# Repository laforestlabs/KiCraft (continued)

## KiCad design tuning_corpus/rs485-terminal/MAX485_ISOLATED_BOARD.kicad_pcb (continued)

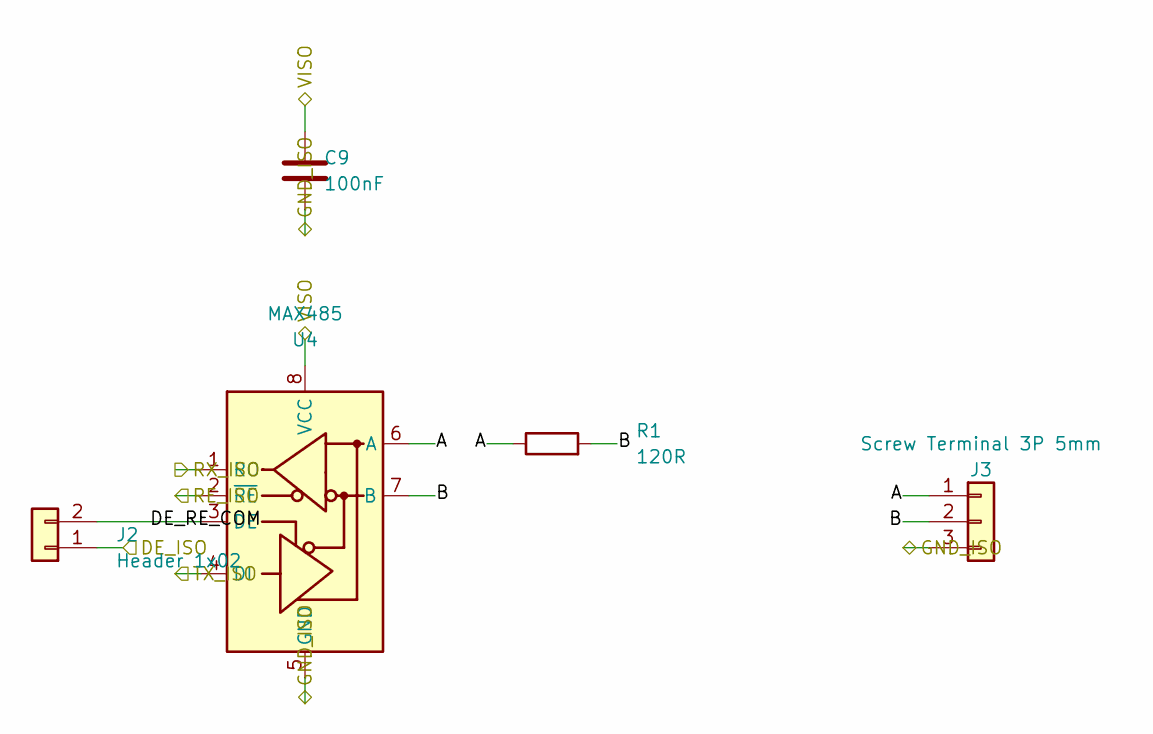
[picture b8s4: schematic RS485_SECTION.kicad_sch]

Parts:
C9: 100nF; C_0805_2012Metric
J2: Header 1x02; PinHeader_1x02_P2.54mm_Vertical
J3: Screw Terminal 3P 5mm; TerminalBlock_MaiXu_MX126-5.0-03P_1x03_P5.00mm
R1: 120R; R_0805_2012Metric
U4: MAX485; SOIC-8_3.9x4.9mm_P1.27mm

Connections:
A: J3.1, R1.1, U4.6 (A)
B: J3.2, R1.2, U4.7 (B)
DE_ISO: J2.1; also elsewhere on the board
DE_RE_COM: J2.2, U4.3 (DE)
GND_ISO: C9.2, J3.3, U4.5 (GND); also elsewhere on the board
RE_ISO: U4.2 (~RE); also elsewhere on the board
RX_ISO: U4.1 (RO); also elsewhere on the board
TX_ISO: U4.4 (DI); also elsewhere on the board
VISO: C9.1, U4.8 (VCC); also elsewhere on the board

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
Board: 2 copper layers, 17 parts (0 on the bottom side), 15 nets, no tracks yet.
